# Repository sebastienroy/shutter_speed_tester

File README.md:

# Shutter Speed Tester for Film Cameras

The shutter speed tester is a project which goal is to design and build a tool that allows to test the shutter speed accuracy of a film camera

When people passionated with old film cameras want to use their camera to shoot film, this sometimes results in an over or an under exposed film.  
This is usually due to the speed of the camera shutter that is not any more accurate. In order to check the shutter speed accuracy, the camera owner has to compare the actual opening time of the shutter with the expected one.  
This is the purpose of the shutter speed tester : measure the accuracy of shutter speed. 

Here is a presentation video (in French) :  

The result of this open source project is to allow anyone who has the minimum skills in DIY domain to build his own device

[Here is the description of the open source project.](project_description.md)

## Accuracy of the open source tester

The resulting tester has been tested against two methods described in [shutter meta tester project](https://github.com/sebastienroy/shutter_meta_tester) : time slot method and rotating wheel method.  
With the time slot method (an LED lit during a given time duration), the difference between expected and measured value is about a few tens of microseconds. This error is due mainly to the latency of the phototransistor. This error is small enough to not to be taken into account even at speed up to 1/2000s.  
With the rotating wheel method, we can observe an error a lot bigger. This error is not due to electronic factors, but results from geometric facts:  
The sensor of the tester is a bulb of 3mm diameter.  
At 1/1000s, given that the curtains translation speed is about 3m/s, the slit width of the curtain shutters is about 3mm large.  
When trying to measure a 3mm object with a 3mm sensor, the resulting error is about 100%.  
**So, because of geometric consideration, the use of such a tester should be reserved for speeds not exceeding 1/250.  
The conclusion is the same for all testers with a similar sensor that do not provide a calibration mechanism.**  

# Baby Shutter Tester mark II
Many people, interested to get such a device but who don't feel skilled enough to build their own copy, asked the author of the project to build it for them.  
This resulted to the commercial version of the tool, the Baby Shutter Tester (mark I).  
The Baby Shutter Tester was regularly improved, and its main additional feature was the ability to self calibrate.  **The self-calibration mechanism allowed a precision of a few microseconds, instead of 1 stop at high speeds.**  
However, the precision brought by the self-calibration procedure required to follow a very specific process, difficult to implement outside a workshop.  

So, a completely reworked version has been designed: the **Baby Shutter Tester Mark II.**  
The speed measurement method impleted by this new version is completely different: instead of starting a timer at a given light illumination threshold, the tester takes into account all the light variations that hits its sensor.  
This allows to take into account high speed ranges, where the shutter cannot be considered as a perfect shutter, i.e. the cases where the shutter cannot be aproximated to an on/off mechanism.  
This method is similar to the method used by the Kyoritsu legacy professional shutter tester.  
Details about the measurement method can be find here:  
https://photographyelectronics.com/methods-for-measuring-shutter-speed/  
The experimental results that confirm the accuracy of the method and of the electronic circuits of the Baby Shutter Tester mkII can be read here;  
https://photographyelectronics.com/experimental-measurement-of-the-shutter-speed-of-a-leaf-shutter/

In addition, the Baby Shutter Tester Marks II meets all the recommendations of the ISO-516:2019 standard. Not only the testing method but also all the measurement precision requirement described by the standard.  

The benefits of this characteristics are the following:
- An extreme accuracy
- The accuracy is obtained without calibration procedure
- Using the optional light source with diffuser, the tester can also measure central (leaf) shutters without any bias.

More information on https://photographyelectronics.com  

## Video presentation

## Accuracy test methods
The accuracy of the Baby Shutter Tester mark II is checked using 
- the graphical verification method described in the ISO-516:2019 standard
- [a dedicated benchmark](https://github.com/sebastienroy/shutter_meta_tester).
 
## Where to buy 
https://photographyelectronics.com/shop/  
[eBay link](https://www.ebay.fr/itm/205397044799)

## User manual

[User Manual](https://github.com/sebastienroy/shutter_speed_tester/wiki/Shutter-Testers-documentation)

# Curtain travel time measurement: The Shutter Lover

The Shutter Lover is a tool specialized in the measurement of the travel time of the curtains of focal plane shutters.  
The measurement of the curtain travel time is necessary for camera repairers, in order to be able to ajust the springs of each of the curtains.  
The goal is to obtain an homogeneous travel time of the two curtains, with values in accordance with the manufacturer recommendations.  

Shop: https://photographyelectronics.com/shop/  
This product is also available for [purchase on ebay](https://www.ebay.fr/itm/204344103169).  

Here is a short teaser :  

## User Manual  

[User Manual](https://github.com/sebastienroy/shutter_speed_tester/wiki/Shutter-Testers-documentation)

## Test bench

In order to get the better precision and reproducibility with the shutter Lover, it is recommended to use a test bench, such as the one describe [here](testbench/testbench.md).

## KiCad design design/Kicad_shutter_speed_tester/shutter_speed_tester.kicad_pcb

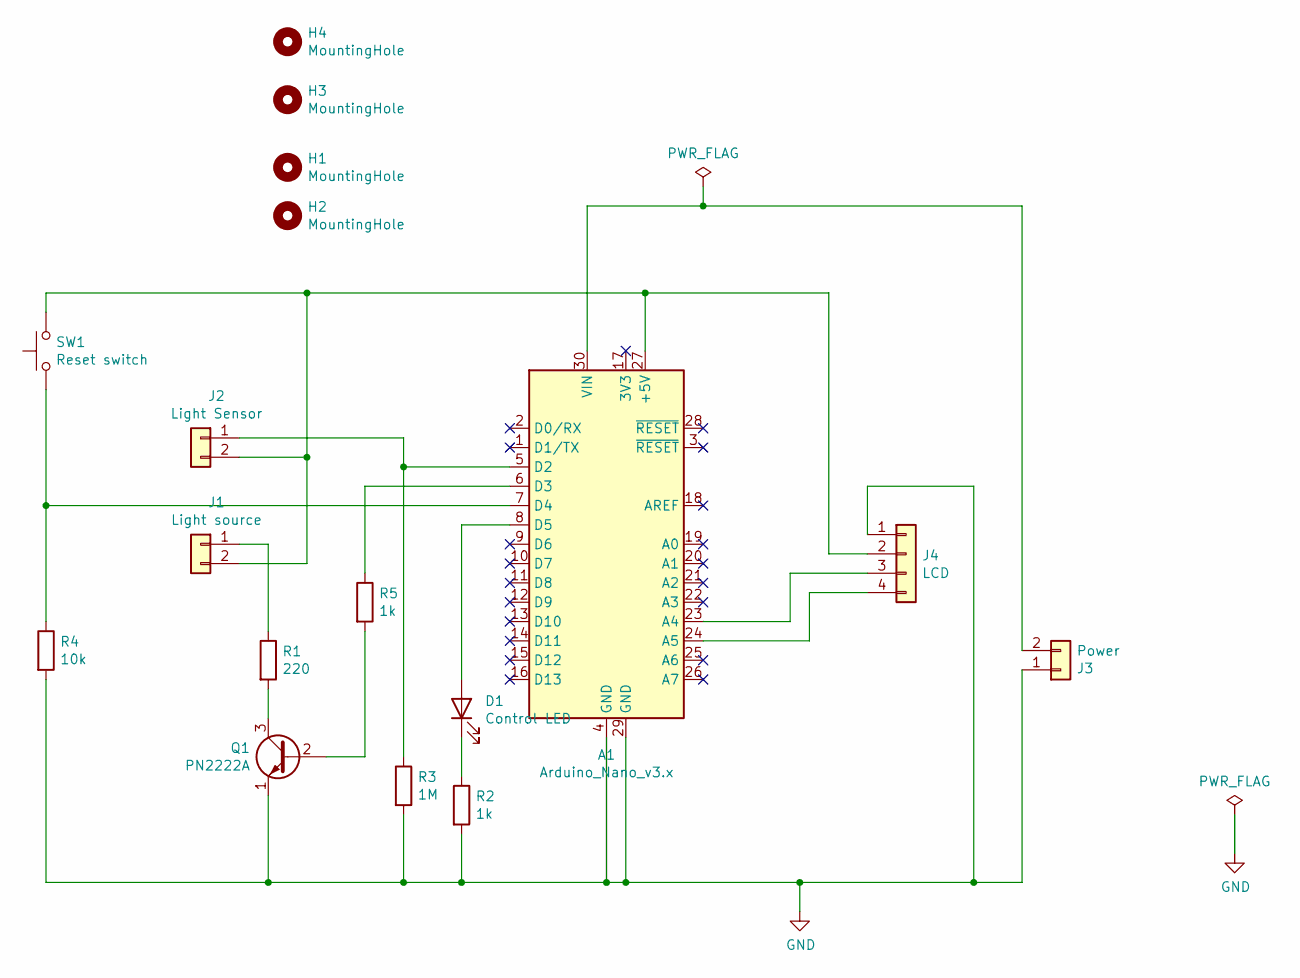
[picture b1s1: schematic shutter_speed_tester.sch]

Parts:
A1: Arduino_Nano_v3.x; Arduino_Nano
D1: Control LED; LED_D5.0mm
H1, H2, H3, H4: MountingHole; MountingHole_2.5mm
J1: Light source; Molex_KK-254_AE-6410-02A_1x02_P2.54mm_Vertical
J2: Light Sensor; Molex_KK-254_AE-6410-02A_1x02_P2.54mm_Vertical
J3: Power; Molex_KK-254_AE-6410-02A_1x02_P2.54mm_Vertical
J4: LCD; Molex_KK-254_AE-6410-04A_1x04_P2.54mm_Vertical
Q1: PN2222A; TO-92_Inline_Wide
R1: 220; R_Axial_DIN0207_L6.3mm_D2.5mm_P7.62mm_Horizontal
R2, R5: 1k; R_Axial_DIN0207_L6.3mm_D2.5mm_P7.62mm_Horizontal
R3: 1M; R_Axial_DIN0207_L6.3mm_D2.5mm_P7.62mm_Horizontal
R4: 10k; R_Axial_DIN0207_L6.3mm_D2.5mm_P7.62mm_Horizontal
SW1: Reset switch; SW_PUSH_6mm_H5mm

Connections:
GND: A1.4 (GND), A1.29 (GND), J3.1, J4.1, Q1.1 (E), R2.2, R3.2, R4.2
unnamed: A1.5 (D2), J2.1, R3.1
unnamed: A1.6 (D3), R5.1
unnamed: A1.7 (D4), R4.1, SW1.1
unnamed: A1.8 (D5), D1.2 (A)
unnamed: A1.23 (A4), J4.3
unnamed: A1.24 (A5), J4.4
unnamed: A1.27 (+5V), J1.2, J2.2, J4.2, SW1.2
unnamed: A1.30 (VIN), J3.2
unnamed: D1.1 (K), R2.1
unnamed: J1.1, R1.1
unnamed: Q1.2 (B), R5.2
unnamed: Q1.3 (C), R1.2

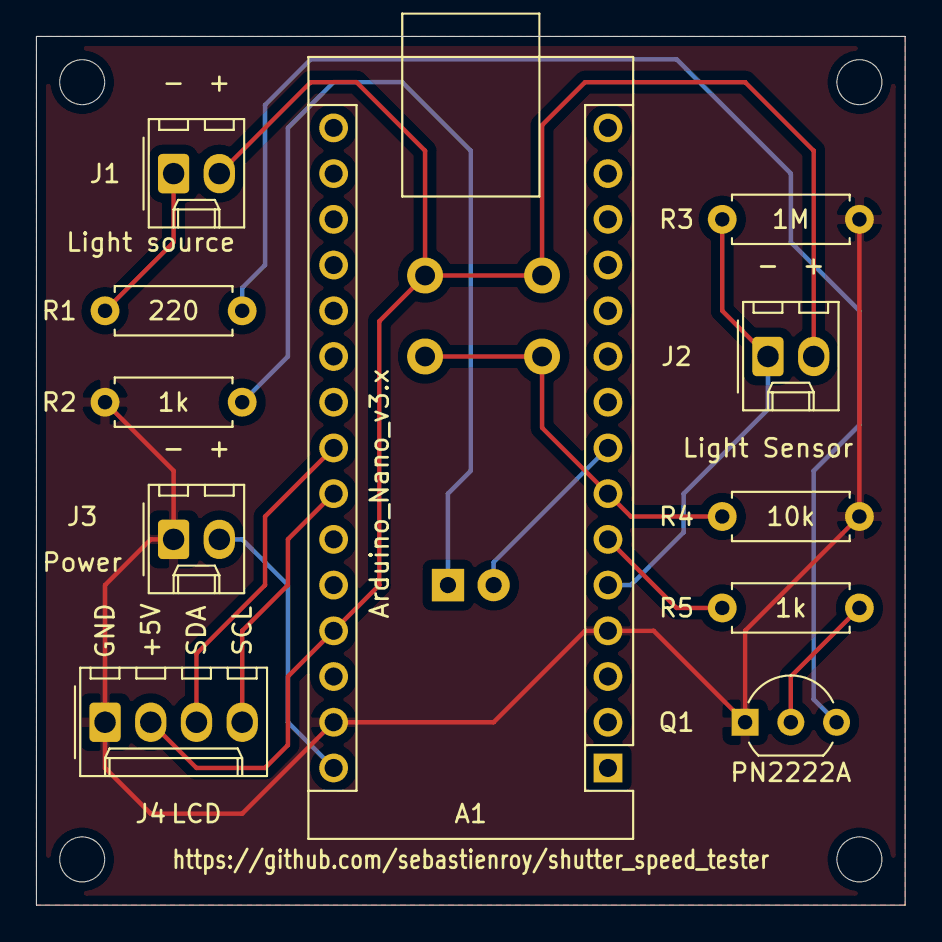
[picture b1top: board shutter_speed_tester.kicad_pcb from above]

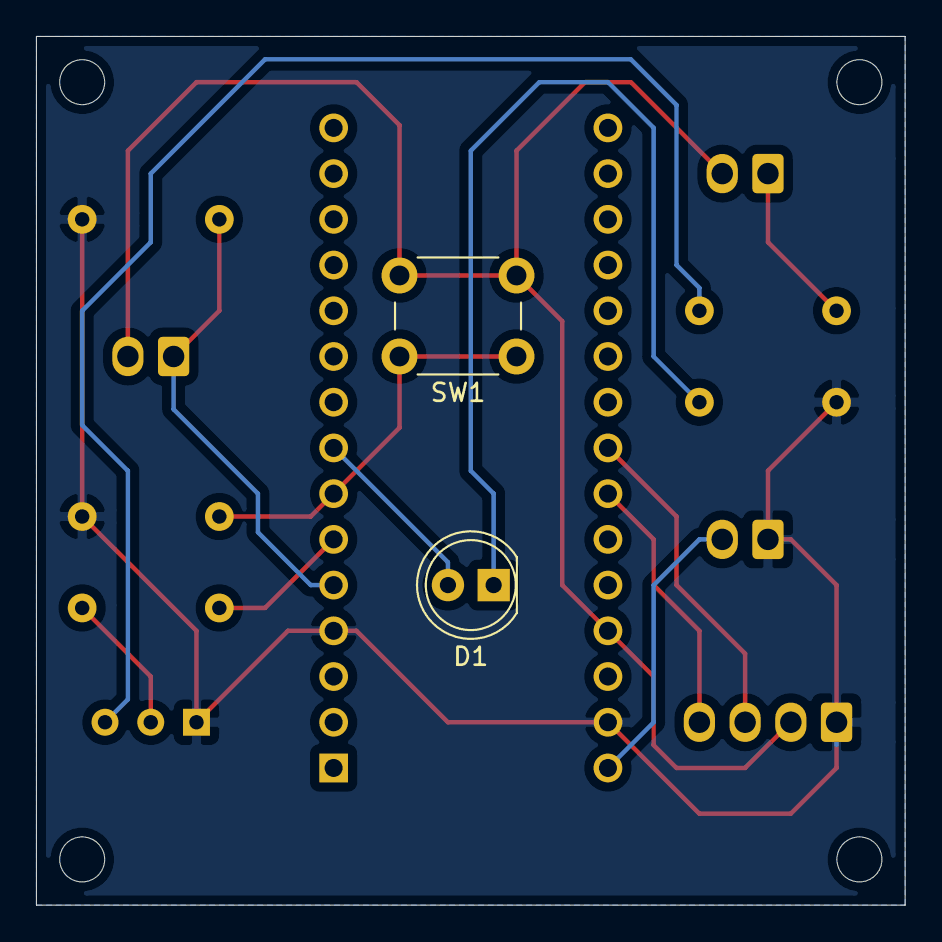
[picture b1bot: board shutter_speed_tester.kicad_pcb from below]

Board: 2 copper layers, 48.3 x 48.3 mm, 17 parts (2 on the bottom side), 13 nets.

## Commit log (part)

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2021-11-07 Work in progress
2021-11-08 Story 1 in progress
2021-11-10 Work in progress : light source description and experimentation step
2021-11-12 Step 0 work in progress
2021-11-12 Step 0 finished
2021-11-12 Step 1 looks fine
2021-11-13 Add state diagram step
2021-11-13 few corrections
2021-11-13 Spellings...
2021-11-13 Spelling...
2021-11-13 Add step 3 : control LED
2021-11-14 Add lcd display
2021-11-14 Few improvemets
2021-11-24 Create LICENSE
2021-11-28 Add kicad files
2021-11-28 adding routing
2021-11-29 pcb design described
2021-11-30 Update part list
2021-12-01 reorganize pcb with USB port on top
2021-12-01 move components
2021-12-04 Remove LCD cursor
2021-12-07 update board
2021-12-12 Changes on PCB, fixes #2, fixes #3, fixes #4
2021-12-13 Add screws in part list
2021-12-16 export pcb 3d view
2021-12-16 few spellings...
2021-12-20 Set control LED size to 5mm
2021-12-20 Add i2c scanner
2021-12-20 Step 7 : Casing fron panel
2021-12-20 Upper casing...
2021-12-22 Fixes #6 : bouncing management
2021-12-22 Casing...
2021-12-22 tests...
2021-12-23 Change phototransistor reference
2021-12-26 work on casing
2021-12-27 work in progress. reduce by depth and add 9V battery
2022-01-02 changes on lightSource housing
2022-01-03 increase tollerance around light source LED
2022-01-04 begin design of battery door
2022-01-04 Battery door is complete
2022-01-04 reduce battery cage
2022-01-04 work on battery door
2022-01-05 Changes on door
2022-01-05 adjust door
2022-01-05 started work on rear panel
2022-01-06 Create Light Sensor Casing
2022-01-06 Beginning of step 10
2022-01-12 update sensorcasing
2022-01-12 Work still in progress
2022-01-13 Add conclusion on battery door design
2022-01-13 Almost finished!
2022-01-13 Reorganisation
2022-01-14 add documentation
2022-01-14 spelling
2022-01-14 6x6 adpter
2022-01-15 description reorganisation
2022-01-15 Description en francais
2022-01-18 operation concepts...
2022-01-18 description in progress
2022-01-18 Add auto update LCD I2C address
2022-01-18 add casing parts
2022-01-19 add USB access hole in the case body
2022-01-20 add datasheets and driver
2022-01-25 Almost finished
2022-01-25 Add PLA filament in part list
2022-01-27 precision on the switch connection
2022-01-27 Allow to run without LCD
2022-01-27 add light sensor casing stories
2022-01-28 allow code to run also on Atmega 168
2022-01-29 increase tolerence between button and panel
2022-01-29 add github reference on rear panel
2022-01-29 sorting parts by color
2022-01-29 add credits
2022-01-31 Remove unused jack audio connector
2022-02-04 Link with YouTube presentation video
2022-02-07 Add indication on the LiquidCrystal I2C library
2022-02-07 update license
2022-02-16 Write userManual (French)
2022-03-09 First presentation of Baby Shutter Tester
2022-03-09 teaser
2022-03-11 add image
2022-03-11 Add baby shutter tester description (fr)
2022-03-13 Add babyShutterTester user manual
2022-03-13 add youtube image
2022-03-13 update links
2022-03-19 add compensation to the hw delay
2022-03-21 Update ebay link
2022-04-24 Change lr6 to lr03(aaa)
2022-07-08 Add indication on the measurement uncertainty
2022-07-08 add precision on measurement accuracy
2023-02-27 Update BabyShutterTester documentation
2023-03-02 update docuentation
2023-05-14 add shutter lover manual
2023-05-14 renaming
2023-05-29 typo
2024-01-04 Update documentation
2024-03-04 Update Baby Shutter Tester manual
2024-03-04 Update manual link
2024-11-04 add testbench description
2024-11-04 add link to the test bench
2024-11-16 add new version of ShutterLover doc
2024-11-16 renaming...
2025-04-04 add mkii manuals
2025-06-14 Improved title for more immediate understanding
    Clarified what this project is about.
2025-06-15 Added FreeCAD assembly screenshot
    Added FreeCAD assembly screenshot to signal its open-soruce nature and modifyability.
